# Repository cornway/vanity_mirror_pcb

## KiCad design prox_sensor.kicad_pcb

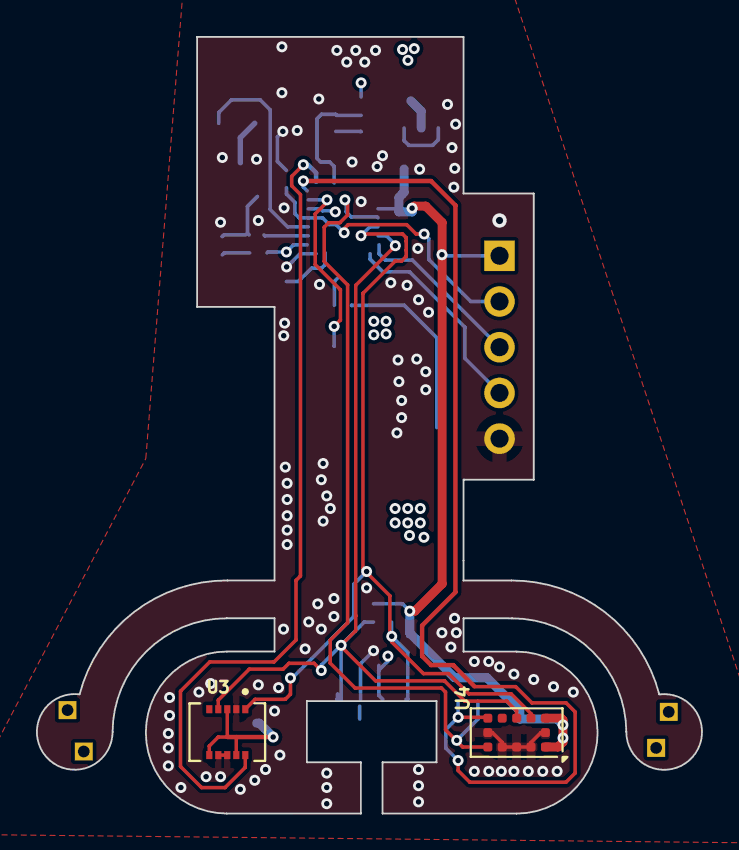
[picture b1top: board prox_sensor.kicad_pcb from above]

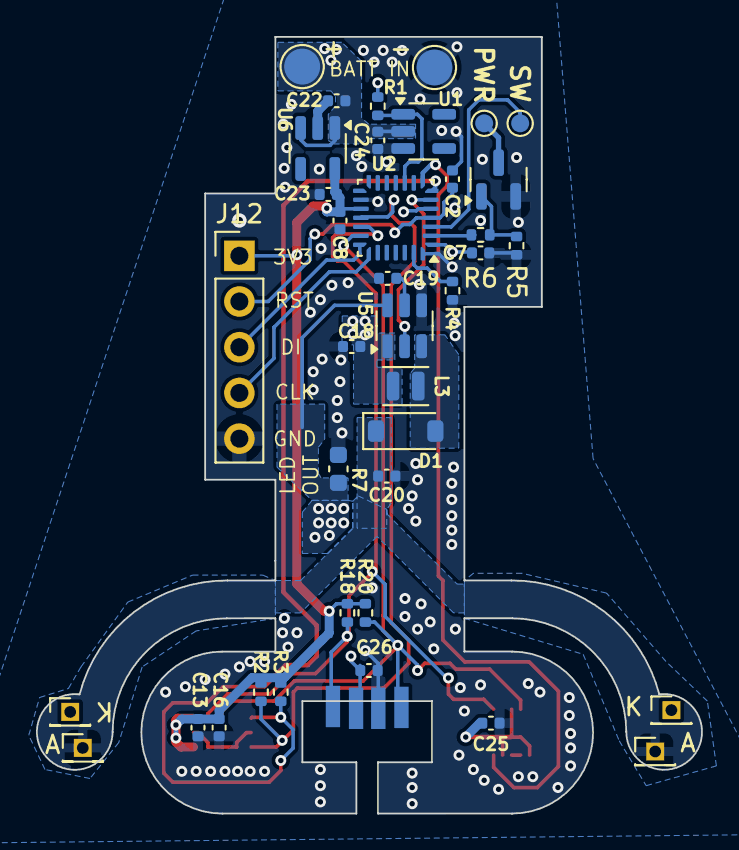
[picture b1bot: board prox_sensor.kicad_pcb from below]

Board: 4 copper layers, 37.0 x 43.1 mm, 41 parts (39 on the bottom side), 22 nets.

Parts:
C2, C8, C16, C24, C25, C26: 100nF/16V; C_0402_1005Metric
C7, C13, C18: 4.7uF/10V; C_0402_1005Metric
C19: 220nF/16V; C_0402_1005Metric
C20, C22, C23: 1uF/25V; C_0402_1005Metric
D1: MBR0540; D_SOD-123
J1: +; TestPoint_Pad_D2.0mm
J2: -; TestPoint_Pad_D2.0mm
J3, J4: A; PinHeader_1x01_P1.27mm_Vertical
J5: -; TestPoint_Pad_D1.0mm
J7: sw; TestPoint_Pad_D1.0mm
J9, J10: K; PinHeader_1x01_P1.27mm_Vertical
J12: Conn_01x05; PinHeader_1x05_P2.54mm_Vertical
L3: 10uH/0.5A; L_Murata_DFE201610P
LED1: LED-SMD_4P-L6.8-W2.4_VEML7700-TR
Q1: AO3400A; SOT-23
R1, R2, R3, R5: 100k; R_0402_1005Metric
R4, R18, R20: 10k; R_0402_1005Metric
R6: 100Ohm; R_0402_1005Metric
R7: 1.3R; C_0603_1608Metric
U1: BD4840G-TR; SOT-23-5
U2: STM32L031G6U6; QFN-28_4x4mm_P0.5mm
U3: STHS34PF80; XDCR_STHS34PF80TR
U4: VL53L0CXV0DH1; ST_VL53L1x
U5: TPS61165DBV; SOT-23-6
U6: NCP718xSN330; SOT-23-5

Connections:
+3V3: C7.1, C8.2, C13.1, C16.2, C23.1, C25.2, C26.2, J12.1, LED1.2 (VDD), R1.2, R2.2, R3.2, R18.2, R20.2, U2.1 (VDD), U2.5 (VDDA), U2.17 (VDD), U3.3 (CS), U3.6 (VDD), U3.9 (VDD), U4.1 (AVDDVCSEL), U4.11 (AVDD), U6.5 (OUT)
+BATT: C18.1, C22.1, C24.2, J1.1, L3.1, U1.2 (VDD), U5.1 (VIN), U6.1 (IN), U6.3 (EN)
/Mcu-unit: STM32/NRST: C2.2, J12.2, U2.4 (NRST)
/Mcu-unit: STM32/PA0_LED_CTRL: U2.6 (PA0), U5.2 (CTRL)
/Mcu-unit: STM32/PA1_ToF_GPIO: R3.1, U2.7 (PA1), U4.7 (GPIO1)
/Mcu-unit: STM32/PA2_STH_GPIO_INT: U2.8 (PA2), U3.10 (INT)
/Mcu-unit: STM32/PA4_LOW_BATT: R1.1, U1.1 (VOUT), U2.10 (PA4)
/Mcu-unit: STM32/PA8_ToF_XSHUT: R2.1, U2.18 (PA8), U4.5 (XSHUT)
/Mcu-unit: STM32/PA9_I2C_SCL: LED1.1 (SCL), R18.1, U2.19 (PA9), U3.1 (SCL), U4.10 (SCL)
/Mcu-unit: STM32/PA10_I2C_SDA: LED1.4 (SDA), R20.1, U2.20 (PA10), U3.4 (SDA), U4.9 (SDA)
/Mcu-unit: STM32/PC_14: R6.2, U2.2 (PC14)
/Mcu-unit: STM32/PC_15: J7.1, U2.3 (PC15)
/Mcu-unit: STM32/SWCLK: J12.4, U2.22 (PA14)
/Mcu-unit: STM32/SWDIO: J12.3, U2.21 (PA13)
/TPS61165/LEDA: C20.1, D1.1 (K), J3.1, J4.1
/TPS61165/LEDK: J9.1, J10.1, R7.1, U5.6 (FB)
GND: C2.1, C7.2, C8.1, C13.2, C16.1, C18.2, C19.2, C20.2, C22.2, C23.2, C24.1, C25.1, C26.1, J2.1, J12.5, LED1.3 (GND), Q1.2 (S), R4.1, R5.2, R7.2, U1.3 (GND), U2.16 (VSS), U2.28 (VSS), U3.2 (RES), U3.7 (GND), U3.8 (GND), U4.2 (AVSSVCSEL), U4.3 (GND), U4.4 (GND), U4.6 (GND), U4.12 (GND), U5.4 (GND), U6.2 (GND)
unnamed: D1.2 (A), L3.2, U5.3 (SW)
unnamed: J5.1, Q1.3 (D)
unnamed: Q1.1 (G), R5.1, R6.1
unnamed: R4.2, U2.27 (BOOT0)
unnamed: C19.1, U5.5 (COMP)

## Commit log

2025-03-21 v3.0
2025-03-21 Rev 4: separating sensors
2025-04-06 Separate sensors, refactoring
2025-04-06 Adding light sensor
2025-04-09 Next iteration
2025-04-14 swdio connector
2025-04-17 Hole for VEML7700
2025-04-18 Refactoring
2025-10-10 Adding power control and extra input, to attach another som
